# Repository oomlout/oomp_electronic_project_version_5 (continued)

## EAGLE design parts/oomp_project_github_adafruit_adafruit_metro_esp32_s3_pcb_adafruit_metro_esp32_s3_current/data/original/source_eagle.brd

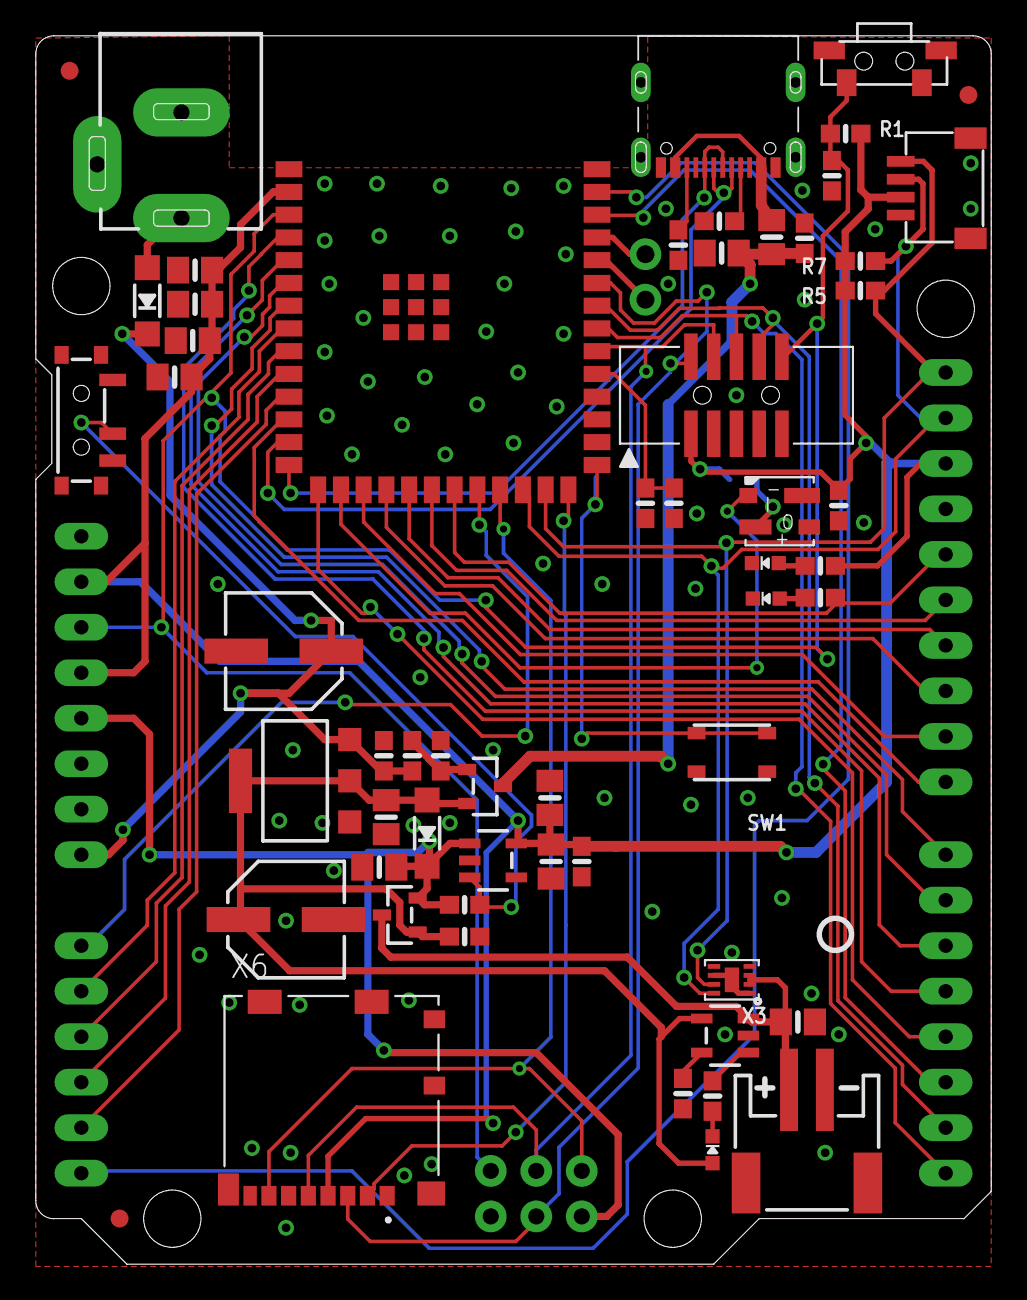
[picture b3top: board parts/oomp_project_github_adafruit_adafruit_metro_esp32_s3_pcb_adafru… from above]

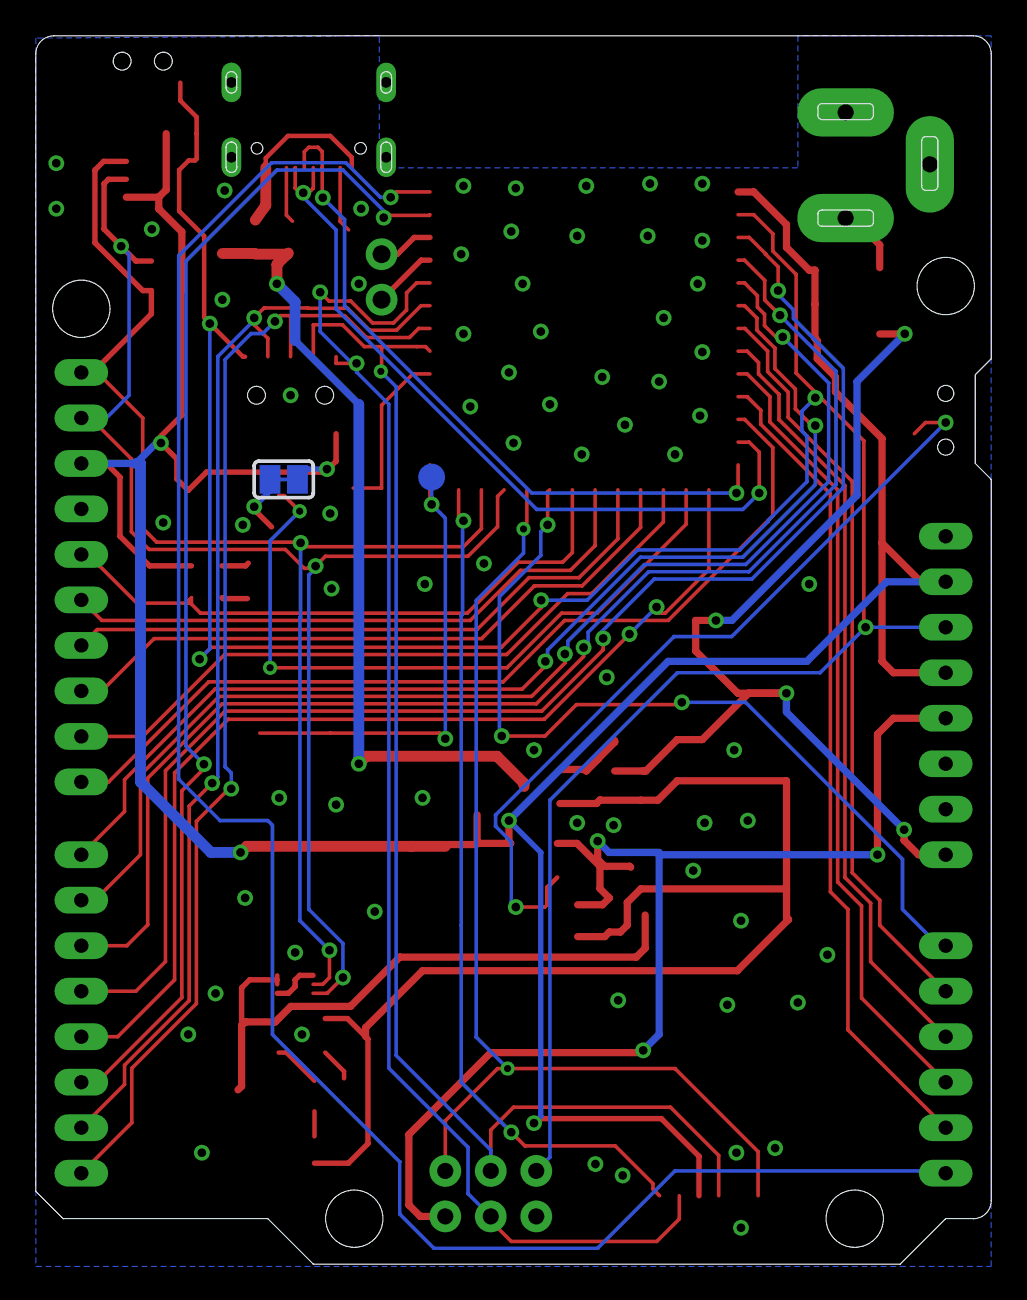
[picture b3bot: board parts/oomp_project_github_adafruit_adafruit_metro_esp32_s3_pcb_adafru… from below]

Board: 2 copper layers, 53.3 x 68.6 mm, 69 parts (3 on the bottom side), 53 nets.

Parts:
AD: 1x6 F; 1X06_OVALWAVE
C1, C3, C4, C7, C8, C10, C11, C13, C17, C18: 10uF; 0805-NO
C2, C12, C15: 0.1uF; 0603-NO
C5, C6, C14: 1uF; 0603-NO
CHG1: ORANGE; CHIPLED_0603_NOOUTLINE
CONN1: STEMMA_I2C_QT; JST_SH4
D1, D4: MBR540; SOD-123
F2: 500mA; 0805-NO
FD1, FD2, FD3: FIDUCIAL_1MM
ICSP: 3x2 M; 2X03_ROUND_70MIL
IOH: 1x10 F; 1X10_OVALWAVE
IOL: 1x8 F; 1X08_OVALWAVE
JP2: UART; 1X02_ROUND
L: RED; CHIPLED_0603_NOOUTLINE
LED1: WS2812B_3535FULL; LED3535_FULLPADS
ON: GREEN; CHIPLED_0603_NOOUTLINE
PC1, PC2: 47uF/25V; PANASONIC_D
POWER: 1x8 F; 1X08_OVALWAVE
Q1, Q2: DMG3415U-7; SOT23-R
R1, R2, R5, R6, R7, R9: 10K; 0603-NO
R3, R8: 5.1K; 0603-NO
R4: 2.2K; 0603-NO
R12, R14, R15, R16: 100K; 0603-NO
R17: 1Meg; 0603-NO
SJ1: SOLDERJUMPER_CLOSEDWIRE
SW1: RKB2; BTN_RKB2_4.6X2.8
SW3: RA_TACT; SPST_TACTILE_RA
SW4: SPDT R/A; SPDT_SMT_SSSS811101
TP1: TESTPOINT_ROUND_1.5MM_NO
U1: NCP1117ST50T3G; SOT223-R
U2: MCP73831T-2ACI/OT; SOT23-5
U4: AP2112(3.3V); SOT23-5
U5: ESP32-S3-WROOM; S3-WROOM32
U$15: PCBFEAT-REV-040
U$52: METROS3_TOP
U$58: METROS3_BOT
X1: JSTPH; JSTPH2_BATT
X2: 2x5 0.05in; 2X05_1.27MM_BOX_POSTS
X3: MAX17048/T; TDFN8_2X2MM
X4: USB C; USB_C_CUSB31-CFM2AX-01-X
X5: 2.1mm; DCJACK_2MM_PTH
X6: MicroSD; MOLEX_104031-0811

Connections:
3.3V: C2.1, C4.1, C5.1, C7.1, C10.1, C13.1, C17.1, C18.1, CONN1.2, IOH.3, POWER.2, POWER.4, R1.2, R5.2, R6.2, R7.2, SJ1.2, U4.5, U5.2, X2.1, X6.4
+5V: C3.2, CHG1.A, D4.A, PC2.+, Q1.1, Q2.2, R14.2, U1.2, U1.4, U2.4
AD0: AD.1, U5.22
AD1: AD.2, U5.8
AD2: AD.3, U5.9
AD3: AD.4, U5.10
AD4: AD.5, U5.11
AD5: AD.6, U5.39
BOOT0: SW1.B, SW1.B', TP1.P$1, U5.27
D2: IOL.6, U5.38
D3: IOL.5, U5.15
D4: IOL.4, U5.4
D5: IOL.3, U5.5
D6: IOL.2, U5.6
D7: IOL.1, U5.7
D8: IOH.10, U5.12
D9: IOH.9, U5.17
D10: IOH.8, U5.18
D11: IOH.7, U5.19
D12: IOH.6, U5.20
D13: IOH.5, R9.2, U5.21
D+: U5.14, X4.A6, X4.B6
D-: U5.13, X4.A7, X4.B7
EN: R12.1, SW4.B, U4.3
GND: C1.2, C2.2, C3.1, C4.2, C5.2, C6.2, C7.2, C8.2, C10.2, C11.2, C12.2, C13.2, C14.2, C15.2, C17.2, C18.2, CONN1.1, CONN1.MT1, CONN1.MT2, ICSP.6, IOH.4, L.C, LED1.4, ON.C, PC1.-, PC2.-, POWER.6, POWER.7, R3.1, R4.2, R8.1, R14.1, R16.1, R17.1, SW1.A, SW1.A', SW3.1, SW3.MT1, SW3.MT2, SW4.C, U1.1, U2.2, U4.2, U5.1, U5.40, U5.P$2, U5.P$3, U5.P$4, U5.P$5, U5.P$6, U5.P$7, U5.P$8, U5.P$9, U5.P$10, X1.1, X2.3, X2.5, X2.7, X2.9, X3.1, X3.4, X3.6, X3.THERMAL, X4.A1B12, X4.B1A12, X5.GND, X5.GNDBREAK, X6.6, X6.10, X6.G1, X6.G2, X6.G3, X6.G4
IO38_DBLTAP: C6.1, R17.2, U5.31
MISO: ICSP.1, U5.23, X6.7
MOSI: ICSP.4, U5.35, X2.2, X6.3
unnamed: L.A, R9.1
unnamed: Q2.1, R15.1, R16.2
unnamed: ON.A, R6.1
unnamed: CHG1.C, R2.1
unnamed: LED1.2, SJ1.1
unnamed: R2.2, U2.1
unnamed: R8.2, X4.A5
unnamed: R3.2, X4.B5
unnamed: R4.1, U2.5
unnamed: F2.1, X4.A4B9, X4.B4A9
NEOPIX: LED1.1, U5.16
PWR: D1.A, X5.PWR
RESET: C14.1, ICSP.5, POWER.3, R1.1, SW3.2, U5.3, X2.10
RXD0: JP2.2, U5.36
SCK: ICSP.3, U5.32, X2.4, X6.5
SCL: CONN1.4, IOH.1, R5.1, U5.25, X3.7
SDA: CONN1.3, IOH.2, R7.1, U5.24, X3.8
SD_CS: U5.26, X6.2
TDI_RX: IOL.7, U5.34, X2.8
TDO_TX: IOL.8, U5.33, X2.6
TXD0: JP2.1, U5.37
VBAT: C8.1, Q1.3, U2.3, X1.2, X3.2, X3.3
VBUS: C1.1, C15.1, F2.2, Q2.3
VHIGH: C11.1, D4.C, ICSP.2, POWER.5, Q1.2, R12.2, U4.1
VIN: C12.1, D1.C, PC1.+, POWER.8, R15.2, U1.3

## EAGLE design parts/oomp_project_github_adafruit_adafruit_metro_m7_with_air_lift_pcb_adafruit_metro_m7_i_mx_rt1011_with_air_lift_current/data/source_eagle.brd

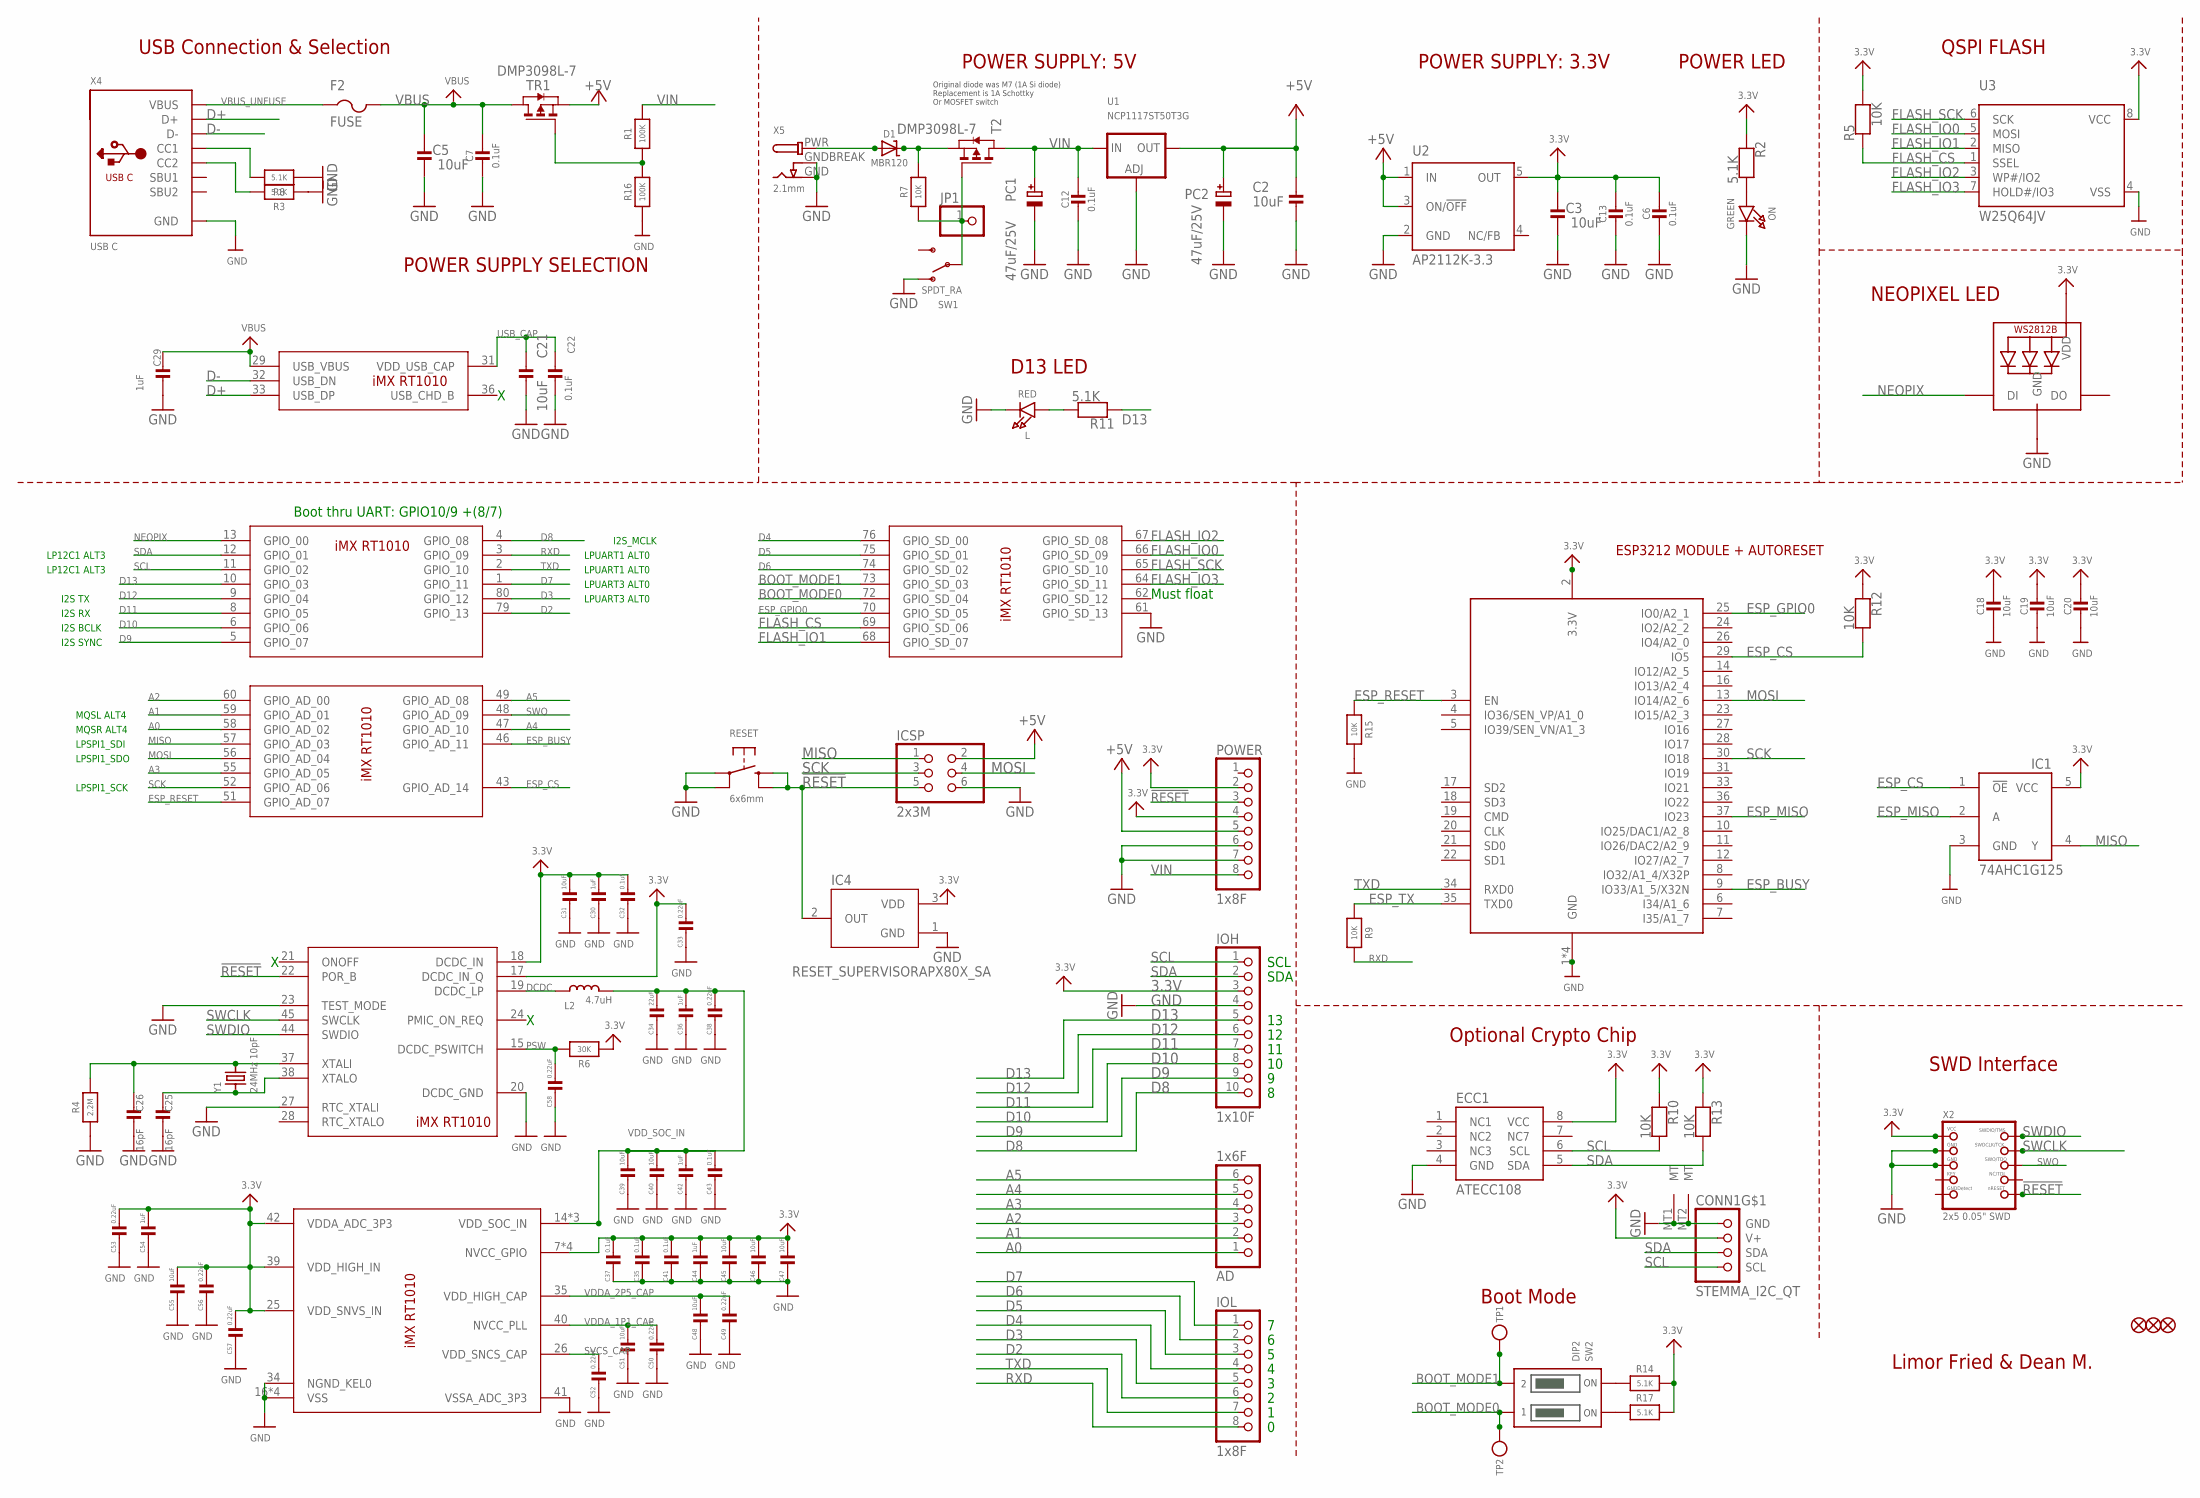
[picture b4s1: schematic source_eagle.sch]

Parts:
AD: 1x6F; 1X06_OVALWAVE
C2, C3, C5, C18, C19, C20, C21, C31, C39, C40, C45, C46, C47, C48, C51, C55: 10uF; 0805-NO
C6, C7, C12, C13, C22, C32, C35, C37, C41, C43: 0.1uF; 0603-NO
C25, C26: 16pF; 0603-NO
C29, C30, C36, C42, C44, C54: 1uF; 0603-NO
C33, C38, C49, C50, C52, C53, C56, C57, C58: 0.22uF; 0603-NO
C34: 22uF; 0805-NO
CONN1: STEMMA_I2C_QT; JST_SH4
D1: MBR120; SOD-123
ECC1: ATECC108; SOIC8
F2: FUSE; R1206
FD1, FD2, FD3: FIDUCIAL_1MM
IC1: 74AHC1G125; SOT23-5L
IC2: IMX_RT1010; QFP50P1400X1400X160-80N
IC4: RESET_SUPERVISORAPX80X_SA; SOT23-WIDE
ICSP: 2x3M; 2X03_ROUND_70MIL
IOH: 1x10F; 1X10_OVALWAVE
IOL: 1x8F; 1X08_OVALWAVE
JP1: HEADER-1X1ROUND; 1X01_ROUND
L: RED; CHIPLED_0603_NOOUTLINE
L2: 4.7uH; INDUCTOR_1007
LED1: WS2812B_3535FULL; LED3535_FULLPADS
ON: GREEN; CHIPLED_0603_NOOUTLINE
PC1, PC2: 47uF/25V; PANASONIC_D
POWER: 1x8F; 1X08_OVALWAVE
R1, R16: 100K; 0603-NO
R2, R3, R8, R11, R14, R17: 5.1K; 0603-NO
R4: 2.2M; 0603-NO
R5, R7, R9, R10, R12, R13, R15: 10K; 0603-NO
R6: 30K; 0603-NO
RESET: 6x6mm; EVQ-Q2_SMALLER
SW1: SPDT_RA; SPDT_SMT_SSSS811101
SW2: DIP2; DIPSWITCH_2PIN
T2: DMP3098L-7; SOT-23
TP1, TP2: TESTPOINTROUND1.5MM; TESTPOINT_ROUND_1.5MM
TR1: DMP3098L-7; SOT-23
U1: NCP1117ST50T3G; SOT223-R
U2: AP2112K-3.3; SOT23-DBV
U3: W25Q64JV; SOIC8_208MIL
X2: 2x5 0.05" SWD; 2X05_1.27MM_BOX_POSTS
X4: USB C; USB_C_CUSB31-CFM2AX-01-X
X5: 2.1mm; DCJACK_2MM_PTH
X6: ESP32_WROOM32; WROOM32
Y1: 24MHz 10pF; CRYSTAL_2.5X2

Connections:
3.3V: C3.2, C6.2, C13.1, C18.1, C19.1, C20.1, C30.1, C31.1, C32.1, C33.1, C35.1, C37.1, C41.1, C44.1, C45.1, C46.1, C47.1, C53.1, C54.1, C55.1, C56.1, C57.1, CONN1.2 (V+), ECC1.8 (VCC), IC1.5 (VCC), IC2.7 (NVCC_GPIO), IC2.17 (DCDC_IN_Q), IC2.18 (DCDC_IN), IC2.25 (VDD_SNVS_IN), IC2.39 (VDD_HIGH_IN), IC2.42 (VDDA_ADC_3P3), IC2.50 (NVCC_GPIO), IC2.63 (NVCC_GPIO), IC2.71 (NVCC_GPIO), IC4.3 (VDD), IOH.3, LED1.2 (VDD), POWER.2, POWER.4, R2.1, R5.2, R6.1, R10.1, R12.1, R13.1, R14.2, R17.2, U2.5 (OUT), U3.8 (VCC), X2.1 (VCC), X6.2 (3.3V)
!RESET: IC2.22 (POR_B), IC4.2 (OUT), ICSP.5, POWER.3, RESET.B (S), RESET.B' (S1), X2.10 (NRESET)
+5V: C2.2, ICSP.2, PC2.+, POWER.5, TR1.2 (S), U1.2 (OUT), U1.4 (OUT), U2.1 (IN), U2.3 (ON/!OFF)
A0: AD.1, IC2.58 (GPIO_AD_02)
A1: AD.2, IC2.59 (GPIO_AD_01)
A2: AD.3, IC2.60 (GPIO_AD_00)
A3: AD.4, IC2.55 (GPIO_AD_05)
A4: AD.5, IC2.47 (GPIO_AD_10)
A5: AD.6, IC2.49 (GPIO_AD_08)
BOOT_MODE0: IC2.72 (GPIO_SD_04), SW2.1OFF, TP2.P$1
BOOT_MODE1: IC2.73 (GPIO_SD_03), SW2.2OFF, TP1.P$1
D2: IC2.79 (GPIO_13), IOL.6
D3: IC2.80 (GPIO_12), IOL.5
D4: IC2.76 (GPIO_SD_00), IOL.4
D5: IC2.75 (GPIO_SD_01), IOL.3
D6: IC2.74 (GPIO_SD_02), IOL.2
D7: IC2.1 (GPIO_11), IOL.1
D8: IC2.4 (GPIO_08), IOH.10
D9: IC2.5 (GPIO_07), IOH.9
D10: IC2.6 (GPIO_06), IOH.8
D11: IC2.8 (GPIO_05), IOH.7
D12: IC2.9 (GPIO_04), IOH.6
D13: IC2.10 (GPIO_03), IOH.5, R11.1
D+: IC2.33 (USB_DP), X4.A6 (D+), X4.B6 (D+)
D-: IC2.32 (USB_DN), X4.A7 (D-), X4.B7 (D-)
DCDC: IC2.19 (DCDC_LP), L2.P$1 (1)
ESP_BUSY: IC2.46 (GPIO_AD_11), X6.9 (IO33/A1_5/X32N)
ESP_CS: IC1.1 (!OE), IC2.43 (GPIO_AD_14), R12.2, X6.29 (IO5)
ESP_GPIO0: IC2.70 (GPIO_SD_05), X6.25 (IO0/A2_1)
ESP_MISO: IC1.2 (A), X6.37 (IO23)
ESP_RESET: IC2.51 (GPIO_AD_07), R15.1, X6.3 (EN)
ESP_TX: R9.1, X6.35 (TXD0)
FLASH_CS: IC2.69 (GPIO_SD_06), R5.1, U3.1 (SSEL)
FLASH_IO0: IC2.66 (GPIO_SD_09), U3.5 (MOSI)
FLASH_IO1: IC2.68 (GPIO_SD_07), U3.2 (MISO)
FLASH_IO2: IC2.67 (GPIO_SD_08), U3.3 (WP#/IO2)
FLASH_IO3: IC2.64 (GPIO_SD_11), U3.7 (HOLD#/IO3)
FLASH_SCK: IC2.65 (GPIO_SD_10), U3.6 (SCK)
GND: C2.1, C3.1, C5.1, C6.1, C7.2, C12.2, C13.2, C18.2, C19.2, C20.2, C21.1, C22.2, C25.2, C26.2, C29.2, C30.2, C31.2, C32.2, C33.2, C34.2, C35.2, C36.2, C37.2, C38.2, C39.2, C40.2, C41.2, C42.2, C43.2, C44.2, C45.2, C46.2, C47.2, C48.2, C49.2, C50.2, C51.2, C52.2, C53.2, C54.2, C55.2, C56.2, C57.2, C58.2, CONN1.1 (GND), CONN1.MT1 (MT), CONN1.MT2 (MT), ECC1.4 (GND), IC1.3 (GND), IC2.16 (VSS), IC2.20 (DCDC_GND), IC2.23 (TEST_MODE), IC2.27 (RTC_XTALI), IC2.30 (VSS), IC2.34 (NGND_KEL0), IC2.41 (VSSA_ADC_3P3), IC2.54 (VSS), IC2.61 (GPIO_SD_13), IC2.78 (VSS), IC4.1 (GND), ICSP.6, IOH.4, L.C, LED1.4 (GND), ON.C, PC1.-, PC2.-, POWER.6, POWER.7, R3.1, R4.1, R8.1, R15.2, R16.1, RESET.A, RESET.A' (P1), SW1.A (O), U1.1 (ADJ), U2.2 (GND), U3.4 (VSS), X2.3 (GND), X2.5 (GND), X4.A1B12 (GND), X4.B1A12 (GND), X5.GND, X5.GNDBREAK, X6.1 (GND), X6.15 (GND), X6.38 (GND), X6.P$1 (GND)
MISO: IC1.4 (Y), IC2.57 (GPIO_AD_03), ICSP.1
MOSI: IC2.56 (GPIO_AD_04), ICSP.4, X6.13 (IO14/A2_6)
unnamed: L.A, R11.2
unnamed: ON.A, R2.2
unnamed: R14.1, SW2.2ON
unnamed: R17.1, SW2.1ON
unnamed: R8.2, X4.A5 (CC1)
unnamed: R3.2, X4.B5 (CC2)
unnamed: C26.1, IC2.37 (XTALI), R4.2, Y1.3 (2)
unnamed: C25.1, IC2.38 (XTALO), Y1.1
unnamed: R1.1, R16.2, TR1.3 (G)
unnamed: D1.C, R7.2, T2.2 (S)
NEOPIX: IC2.13 (GPIO_00), LED1.1 (DI)
PSW: C58.1, IC2.15 (DCDC_PSWITCH), R6.2
PWRIN: D1.A, X5.PWR
PWR_SWITCH: JP1.1, R7.1, SW1.B, T2.3 (G)
RXD: IC2.3 (GPIO_09), IOL.8, R9.2
SCK: IC2.52 (GPIO_AD_06), ICSP.3, X6.30 (IO18)
SCL: CONN1.4 (SCL), ECC1.6 (SCL), IC2.11 (GPIO_02), IOH.1, R10.2
SDA: CONN1.3 (SDA), ECC1.5 (SDA), IC2.12 (GPIO_01), IOH.2, R13.2
SVCS_CAP: C52.1, IC2.26 (VDD_SNCS_CAP)
SWCLK: IC2.45 (SWCLK), X2.4 (SWDCLK)
SWDIO: IC2.44 (SWDIO), X2.2 (SWDIO)
SWO: IC2.48 (GPIO_AD_09), X2.6 (SWO)
TXD: IC2.2 (GPIO_10), IOL.7, X6.34 (RXD0)
USB_CAP: C21.2, C22.1, IC2.31 (VDD_USB_CAP)
VBUS: C5.2, C7.1, C29.1, F2.2, IC2.29 (USB_VBUS), TR1.1 (D)
VBUS_UNFUSE: F2.1, X4.A4B9 (VBUS), X4.B4A9 (VBUS)
VDDA_1P1_CAP: C50.1, C51.1, IC2.40 (NVCC_PLL)
VDDA_2P5_CAP: C48.1, C49.1, IC2.35 (VDD_HIGH_CAP)
VDD_SOC_IN: C34.1, C36.1, C38.1, C39.1, C40.1, C42.1, C43.1, IC2.14 (VDD_SOC_IN), IC2.53 (VDD_SOC_IN), IC2.77 (VDD_SOC_IN), L2.P$2 (2)
VIN: C12.1, PC1.+, POWER.8, R1.2, T2.1 (D), U1.3 (IN)

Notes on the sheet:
SDA
SCL
Limor Fried & Dean M.
Original diode was M7 (1A Si diode) Replacement is 1A Schottky Or MOSFET switch
POWER SUPPLY: 5V
USB Connection & Selection
POWER SUPPLY: 3.3V
POWER LED
POWER SUPPLY SELECTION
D13 LED
NEOPIXEL LED
QSPI FLASH
SWD Interface
ESP3212 MODULE + AUTORESET
Optional Crypto Chip
Boot Mode
Must float
Boot thru UART: GPIO10/9 +(8/7)
LPSPI1_SCK
LPSPI1_SDI
LPSPI1_SDO
LP12C1 ALT3
LPUART1 ALT0
MQSL ALT4
MQSR ALT4
I2S BCLK
I2S SYNC
I2S RX
I2S TX
I2S_MCLK
LPUART3 ALT0

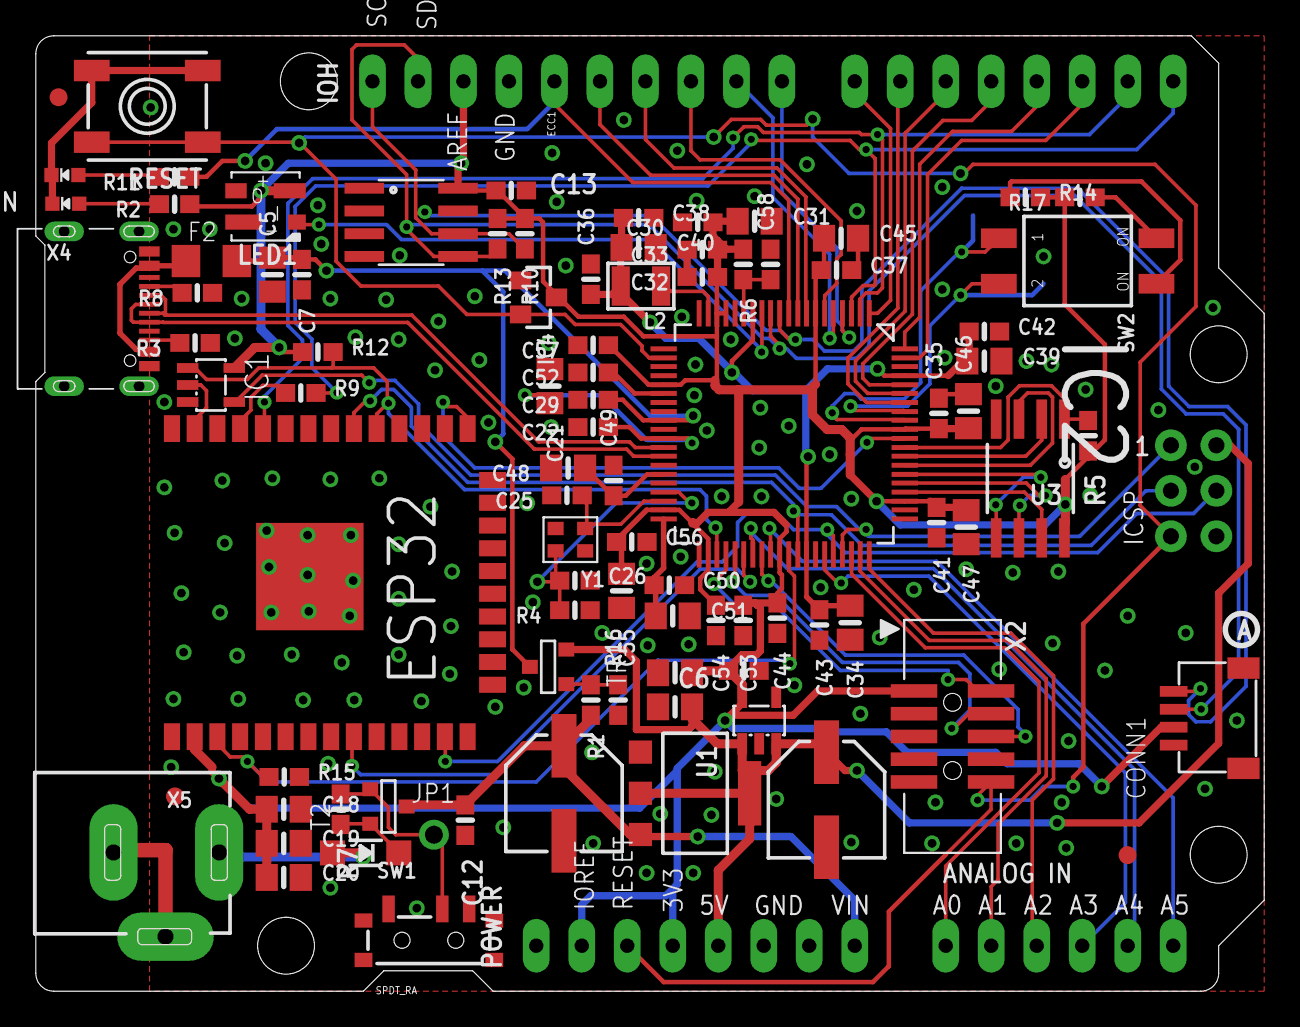
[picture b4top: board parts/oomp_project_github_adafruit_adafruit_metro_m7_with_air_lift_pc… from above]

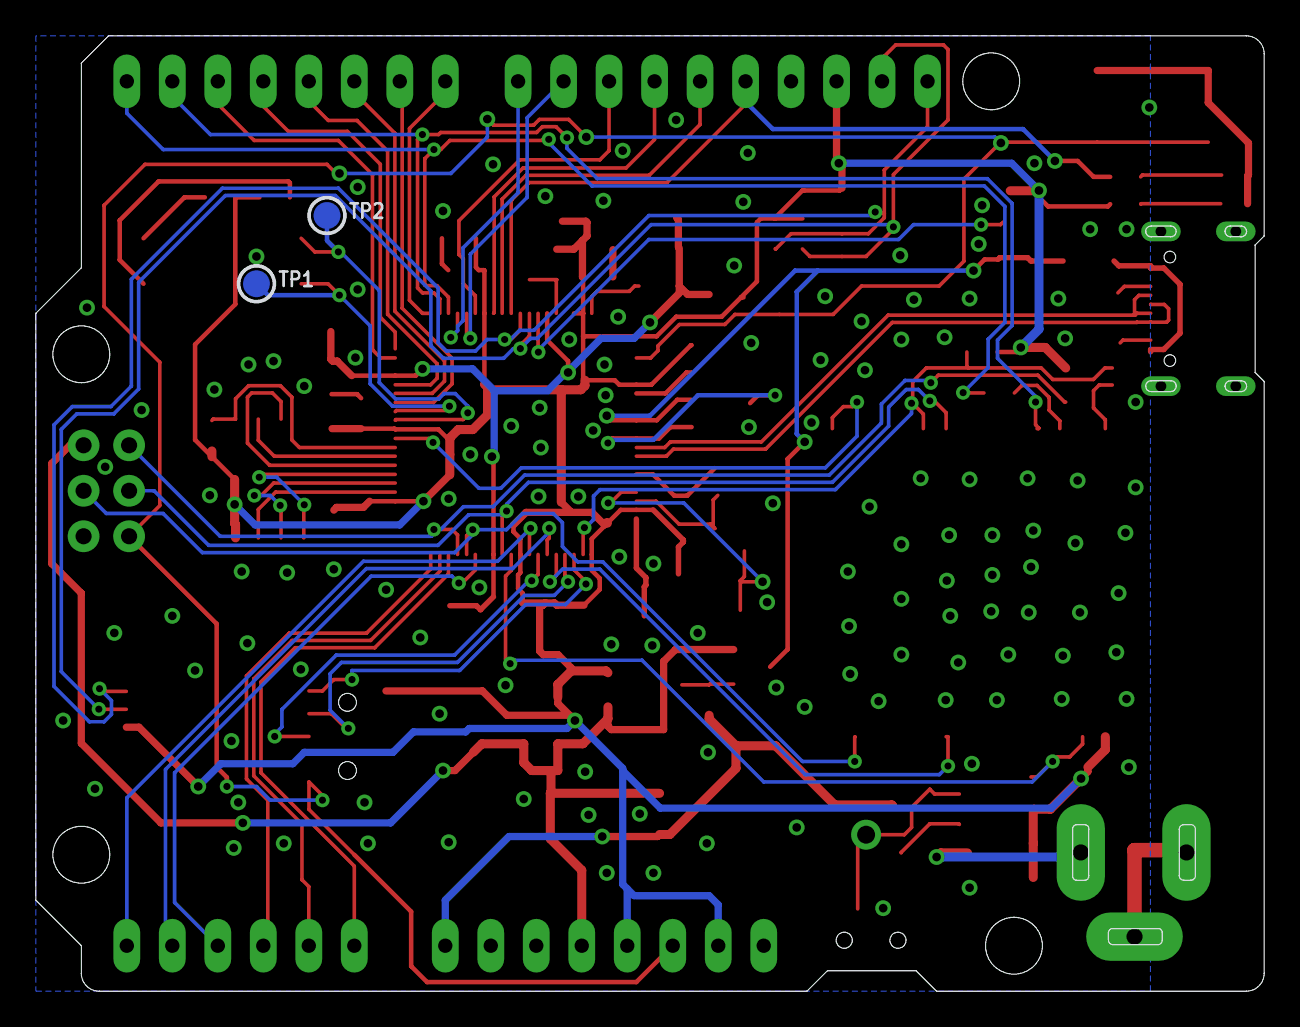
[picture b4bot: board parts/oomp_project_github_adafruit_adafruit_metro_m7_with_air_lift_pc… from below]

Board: 2 copper layers, 68.6 x 53.3 mm, 101 parts (3 on the bottom side), 71 nets.

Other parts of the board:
U$11: PCBFEAT-REV-040
U$12: METROM7_RT1011AIR_BOT
U$18: METROM7_RT1011AIR_TOP

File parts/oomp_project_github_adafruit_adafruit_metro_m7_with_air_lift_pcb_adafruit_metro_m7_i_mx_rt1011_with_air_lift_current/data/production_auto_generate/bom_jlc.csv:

Comment,Designator,Footprint,LCSC Part #
,JP1,Adafruit Metro M7 iMX RT1011 with AirLift-import-fps:1X01_ROUND,C7501259
,U$12,Adafruit Metro M7 iMX RT1011 with AirLift-import-fps:METROM7_RT1011AIR_BOT,
,U$18,Adafruit Metro M7 iMX RT1011 with AirLift-import-fps:METROM7_RT1011AIR_TOP,
,U$11,Adafruit Metro M7 iMX RT1011 with AirLift-import-fps:PCBFEAT-REV-040,
,"TP1,TP2",Adafruit Metro M7 iMX RT1011 with AirLift-import-fps:TESTPOINT_ROUND_1.5MM,
0.1uF,"C6,C7,C12,C13,C22,C32,C35,C37,C41,C43",Adafruit Metro M7 iMX RT1011 with AirLift-import-fps:0603-NO,C14663
0.22uF,"C33,C38,C49,C50,C52,C53,C56,C57,C58",Adafruit Metro M7 iMX RT1011 with AirLift-import-fps:0603-NO,
100K,"R1,R16",Adafruit Metro M7 iMX RT1011 with AirLift-import-fps:0603-NO,C25803
10K,"R5,R7,R9,R10,R12,R13,R15",Adafruit Metro M7 iMX RT1011 with AirLift-import-fps:0603-NO,C98220
10uF,"C2,C3,C5,C18,C19,C20,C21,C31,C39,C40,C45,C46,C47,C48,C51,C55",Adafruit Metro M7 iMX RT1011 with AirLift-import-fps:0805-NO,
16pF,"C25,C26",Adafruit Metro M7 iMX RT1011 with AirLift-import-fps:0603-NO,
1uF,"C29,C30,C36,C42,C44,C54",Adafruit Metro M7 iMX RT1011 with AirLift-import-fps:0603-NO,C5673
1x10F,IOH0,Adafruit Metro M7 iMX RT1011 with AirLift-import-fps:1X10_OVALWAVE,C57369
1x6F,AD0,Adafruit Metro M7 iMX RT1011 with AirLift-import-fps:1X06_OVALWAVE,C37208
1x8F,"IOL0,POWER0",Adafruit Metro M7 iMX RT1011 with AirLift-import-fps:1X08_OVALWAVE,C492421
2.1mm,X5,Adafruit Metro M7 iMX RT1011 with AirLift-import-fps:DCJACK_2MM_PTH,
2.2M,R4,Adafruit Metro M7 iMX RT1011 with AirLift-import-fps:0603-NO,C2933170
22uF,C34,Adafruit Metro M7 iMX RT1011 with AirLift-import-fps:0805-NO,
24MHz 10pF,Y1,Adafruit Metro M7 iMX RT1011 with AirLift-import-fps:CRYSTAL_2.5X2,
2x3M,ICSP0,Adafruit Metro M7 iMX RT1011 with AirLift-import-fps:2X03_ROUND_70MIL,
"2x5 0.05"" SWD",X2,Adafruit Metro M7 iMX RT1011 with AirLift-import-fps:2X05_1.27MM_BOX_POSTS,
30K,R6,Adafruit Metro M7 iMX RT1011 with AirLift-import-fps:0603-NO,
4.7uH,L2,Adafruit Metro M7 iMX RT1011 with AirLift-import-fps:INDUCTOR_1007,
47uF/25V,"PC1,PC2",Adafruit Metro M7 iMX RT1011 with AirLift-import-fps:PANASONIC_D,
5.1K,"R2,R3,R8,R11,R14,R17",Adafruit Metro M7 iMX RT1011 with AirLift-import-fps:0603-NO,C23186
6x6mm,RESET0,Adafruit Metro M7 iMX RT1011 with AirLift-import-fps:EVQ-Q2_SMALLER,
74AHC1G125,IC1,Adafruit Metro M7 iMX RT1011 with AirLift-import-fps:SOT23-5L,
AP2112K-3.3,U2,Adafruit Metro M7 iMX RT1011 with AirLift-import-fps:SOT23-DBV,
ATECC108,ECC1,Adafruit Metro M7 iMX RT1011 with AirLift-import-fps:SOIC8,
DIP2,SW2,Adafruit Metro M7 iMX RT1011 with AirLift-import-fps:DIPSWITCH_2PIN,
DMP3098L-7,"T2,TR1",Adafruit Metro M7 iMX RT1011 with AirLift-import-fps:SOT-23,
ESP32_WROOM32,X6,Adafruit Metro M7 iMX RT1011 with AirLift-import-fps:WROOM32,
FIDUCIAL_1MM,"FD1,FD2,FD3",Adafruit Metro M7 iMX RT1011 with AirLift-import-fps:FIDUCIAL_1MM,
FUSE,F2,Adafruit Metro M7 iMX RT1011 with AirLift-import-fps:R1206,
GREEN,ON0,Adafruit Metro M7 iMX RT1011 with AirLift-import-fps:CHIPLED_0603_NOOUTLINE,
IMX_RT1010,IC2,Adafruit Metro M7 iMX RT1011 with AirLift-import-fps:QFP50P1400X1400X160-80N,
MBR120,D1,Adafruit Metro M7 iMX RT1011 with AirLift-import-fps:SOD-123,
NCP1117ST50T3G,U1,Adafruit Metro M7 iMX RT1011 with AirLift-import-fps:SOT223-R,
RED,L0,Adafruit Metro M7 iMX RT1011 with AirLift-import-fps:CHIPLED_0603_NOOUTLINE,
RESET_SUPERVISORAPX80X_SA,IC4,Adafruit Metro M7 iMX RT1011 with AirLift-import-fps:SOT23-WIDE,
SPDT_RA,SW1,Adafruit Metro M7 iMX RT1011 with AirLift-import-fps:SPDT_SMT_SSSS811101,
STEMMA_I2C_QT,CONN1,Adafruit Metro M7 iMX RT1011 with AirLift-import-fps:JST_SH4,C160404
USB C,X4,Adafruit Metro M7 iMX RT1011 with AirLift-import-fps:USB_C_CUSB31-CFM2AX-01-X,
W25Q64JV,U3,Adafruit Metro M7 iMX RT1011 with AirLift-import-fps:SOIC8_208MIL,
WS2812B_3535FULL,LED1,Adafruit Metro M7 iMX RT1011 with AirLift-import-fps:LED3535_FULLPADS,

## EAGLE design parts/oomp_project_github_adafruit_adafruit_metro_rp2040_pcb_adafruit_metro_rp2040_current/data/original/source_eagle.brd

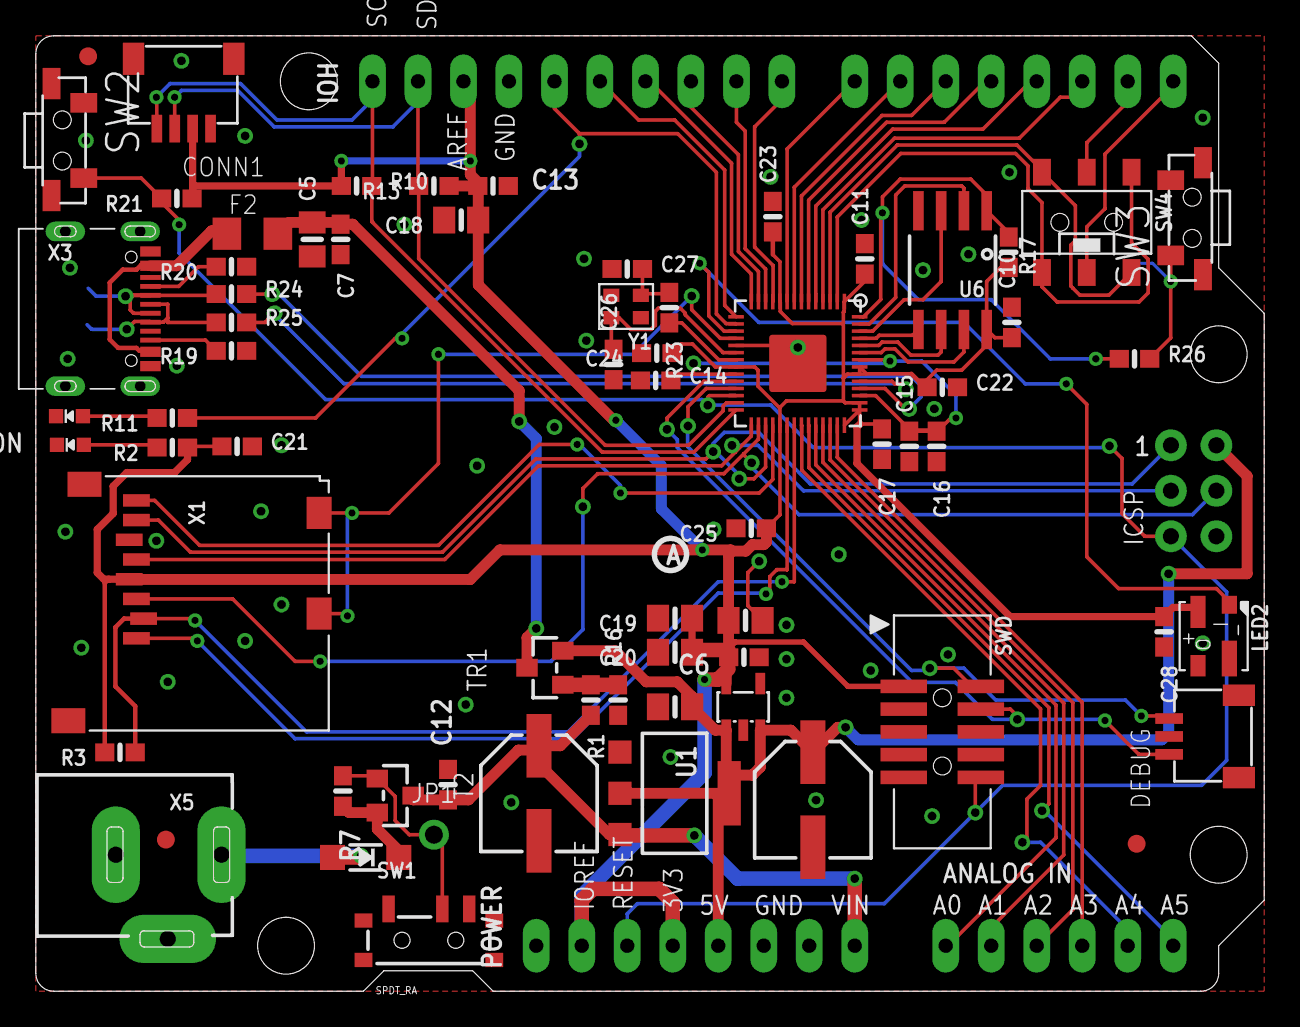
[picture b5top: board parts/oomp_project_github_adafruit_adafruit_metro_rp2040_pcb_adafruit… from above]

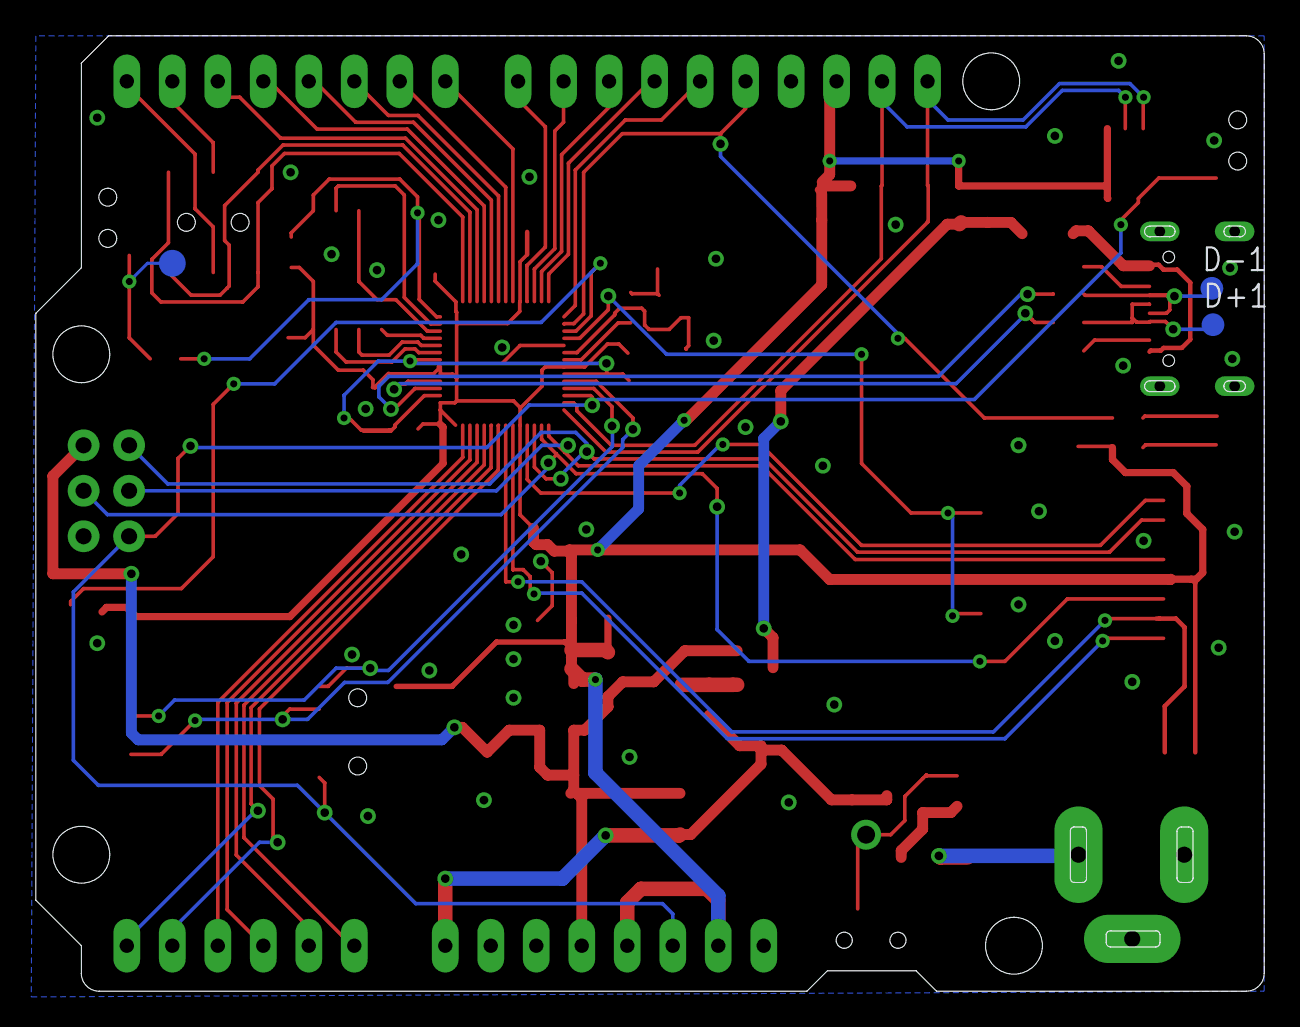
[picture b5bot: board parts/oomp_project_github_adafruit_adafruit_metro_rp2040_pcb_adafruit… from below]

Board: 2 copper layers, 68.6 x 53.3 mm, 79 parts (4 on the bottom side), 64 nets.

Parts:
AD: 20609; 1X06_OVALWAVE
C2, C3, C5, C18, C19, C20: 10uF; 0805-NO
C6, C7, C10, C12, C13, C14, C15, C17, C21, C22, C23, C24, C25: 0.1uF; 0603-NO
C11, C16, C28: 1uF; 0603-NO
C26, C27: 22pF; 0603-NO
CONN1: STEMMA_I2C_QT; JST_SH4
D1: MBR120; SOD-123
D+1: TPB1,27; B1,27
D-1: TPB1,27; B1,27
DEBUG: JST_SH3
F2: FUSE; R1206
FD1, FD2, FD3: FIDUCIAL_1MM
IC2: RP2040_QFN56; QFN56_7MM_REDUCEDEPAD
ICSP: 3x2 M; 2X03_ROUND_70MIL
IOH: 20611; 1X10_OVALWAVE
IOL: 20610; 1X08_OVALWAVE
JP1: 1X01_ROUND
L: RED; CHIPLED_0603_NOOUTLINE
LED2: WS2812B_3535FULL; LED3535_FULLPADS
ON: GREEN; CHIPLED_0603_NOOUTLINE
PC1, PC2: 47uF/25V; PANASONIC_D
POWER: 20610; 1X08_OVALWAVE
R1, R16: 100K; 0603-NO
R2, R11, R19, R20: 5.1K; 0603-NO
R3, R7, R10, R13, R17, R21: 10K; 0603-NO
R23, R26: 1K; 0603-NO
R24, R25: 22 ohm; 0603-NO
SW1: SPDT_RA; SPDT_SMT_SSSS811101
SW2, SW3: SW_RA; SPST_TACTILE_RA
SW4: DPDT; EG1390
SWD: 2x5_0.5IN; 2X05_1.27MM_BOX_POSTS
T2: DMP3098L; SOT23-WIDE
TP1: TESTPOINT_ROUND_1.5MM_NO
TR1: DMP3098L; SOT23-WIDE
U1: NCP1117ST50T3G; SOT223-R
U2: AP2112K-3.3; SOT23-DBV
U6: W25Q128; SOIC8_208MIL
U$11: PCBFEAT-REV-040
U$15: METRO_RP2040_BOT
U$29: METRO_RP2040_TOP
X1: MICROSD
X3: USB Type C; USB_C_CUSB31-CFM2AX-01-X
X5: 2.1mm; DCJACK_2MM_PTH
Y1: 12MHz_12pF; CRYSTAL_2.5X2

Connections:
1.2V: C14.2, C15.2, C16.1, IC2.23, IC2.45, IC2.50
3.3V: C3.2, C6.2, C10.1, C11.1, C13.1, C17.1, C18.1, C19.1, C20.1, C21.1, C22.1, C23.1, C24.1, C25.1, C28.1, CONN1.2, IC2.1, IC2.10, IC2.22, IC2.33, IC2.42, IC2.43, IC2.44, IC2.48, IC2.49, IOH.3, LED2.2, POWER.2, POWER.4, R2.1, R3.2, R10.1, R13.1, R17.2, R21.1, SWD.1, U2.5, U6.8, X1.4
!RESET: IC2.26, ICSP.5, POWER.3, R21.2, SW2.2, SWD.10
+5V: C2.2, ICSP.2, PC2.+, POWER.5, TR1.2, U1.2, U1.4, U2.1, U2.3
A0: AD.1, IC2.38
A1: AD.2, IC2.39
A2: AD.3, IC2.40
A3: AD.4, IC2.41
CC1: R20.2, X3.A5
CC2: R19.2, X3.B5
D0: IC2.2, SW4.O2, SW4.S1
D1: IC2.3, SW4.O1, SW4.S2
D2: IC2.4, IOL.6
D3: IC2.5, IOL.5
D4: IC2.6, IOL.4
D5: IC2.7, IOL.3
D6: IC2.8, IOL.2
D7: IC2.9, IOL.1
D8: IC2.11, IOH.10
D9: IC2.12, IOH.9
D10: IC2.13, IOH.8
D11: IC2.14, IOH.7
D12: IC2.15, IOH.6
D13: IC2.16, IOH.5, R11.1
D24: AD.5, IC2.36
D25: AD.6, IC2.37
D+: IC2.47, R25.2
D-: IC2.46, R24.2
GND: C2.1, C3.1, C5.1, C6.1, C7.2, C10.2, C11.2, C12.2, C13.2, C14.1, C15.1, C16.2, C17.2, C18.2, C19.2, C20.2, C21.2, C22.2, C23.2, C24.2, C25.2, C26.1, C27.1, C28.2, CONN1.1, CONN1.MT1, CONN1.MT2, DEBUG.2, DEBUG.MT1, DEBUG.MT2, IC2.19, IC2.P$1, ICSP.6, IOH.4, L.C, LED2.4, ON.C, PC1.-, PC2.-, POWER.6, POWER.7, R16.1, R19.1, R20.1, SW1.A, SW2.1, SW2.MT1, SW2.MT2, SW3.2, SW3.MT1, SW3.MT2, SWD.3, SWD.5, SWD.7, SWD.9, U1.1, U2.2, U6.4, X1.6, X1.MT1, X1.MT2, X3.A1B12, X3.B1A12, X5.GND, X5.GNDBREAK
MISO/SDIO_DAT0: IC2.31, ICSP.1, X1.7
MOSI/SDIO_CMD: IC2.30, ICSP.4, X1.3
unnamed: L.A, R11.2
unnamed: ON.A, R2.2
unnamed: C26.2, IC2.20, Y1.3
unnamed: C27.2, R23.1, Y1.1
unnamed: R1.1, R16.2, TR1.1
unnamed: IC2.21, R23.2
unnamed: D1.C, R7.2, T2.2
NEOPIX: IC2.17, LED2.1
PWRIN: D1.A, X5.PWR
PWR_SWITCH: JP1.1, R7.1, SW1.B, T2.1
QSPI_CS: IC2.56, R17.1, R26.1, U6.1
QSPI_DATA[0]: IC2.53, U6.5
QSPI_DATA[1]: IC2.55, U6.2
QSPI_DATA[2]: IC2.54, U6.3
QSPI_DATA[3]: IC2.51, U6.7
QSPI_SCK: IC2.52, U6.6
RXD: IOL.8, SW4.P1
SCK/SDIO_CLK: IC2.29, ICSP.3, X1.5
SCL: CONN1.4, IC2.28, IOH.1, R10.2
SDA: CONN1.3, IC2.27, IOH.2, R13.2
SDCS/SDIO_DAT3: IC2.35, R3.1, X1.2
SDIO_DAT1: IC2.32, X1.8
SDIO_DAT2: IC2.34, X1.1
SD_CD: IC2.18, X1.CD1, X1.CD2
SWCLK: DEBUG.1, IC2.24, SWD.4
SWDIO: DEBUG.3, IC2.25, SWD.2
TXD: IOL.7, SW4.P2
USBBOOT: R26.2, SW3.1, TP1.P$1
USB_D+: D+1.TP, R25.1, X3.A6, X3.B6
USB_D-: D-1.TP, R24.1, X3.A7, X3.B7
VBUS: C5.2, C7.1, F2.2, TR1.3
VBUS_UNFUSE: F2.1, X3.A4B9, X3.B4A9
VIN: C12.1, PC1.+, POWER.8, R1.2, T2.3, U1.3
